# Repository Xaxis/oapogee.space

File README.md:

# oApogee

An open source telemetry payload for model rockets, and the documentation that
teaches you to build one. Site at **[oapogee.space](https://oapogee.space)**.

oApogee records altitude, acceleration and orientation through a flight, logs it
to onboard flash, and optionally downlinks it live over LoRa and reports GNSS
position for recovery. It attaches to a rocket you already own, in a printed pod
that needs no modification to the airframe.

**oApogee is a passive instrumentation payload. It does not fire ejection
charges, control deployment, ignite motors, or command any pyrotechnic device.**
That is a design boundary and it will not change. See
[content/safety.md](content/safety.md).

## Project status

**Nothing physical exists.** No board has been fabricated, assembled, weighed,
priced, or flown, so every cost, mass, range and endurance figure is missing
rather than estimated. Each gap is marked in place, on the page that would
otherwise state the figure, rather than summarised on a page of its own: a count
drifts, a marker beside the number it replaces does not.

What does exist is further along than a paper design. The circuit is source that
routes; the firmware is sixteen host-testable modules with a test suite in CI;
the two wire formats are published specifications with a second implementation
checked against the first byte for byte; the printed parts are parametric
source. No fabrication package is published, because the check that gates it
refuses while the board has an open blocker, and it does.

Design decisions that are still open are in
[docs/open-questions.md](docs/open-questions.md).

## The rule everything else follows from

**Never publish a number that has not been measured or sourced.**

The documentation is the product. The hardware is commodity: barometer, IMU,
microcontroller, radio, all of it available to anyone. What makes this project
worth existing is that a motivated beginner can follow the site start to finish
and end up with a working payload and a real flight graph. That only works if
every number on it is true.

So there are no estimates dressed as measurements, and that is enforced rather
than promised: `make prose` fails on any physical quantity in published prose
that is not either recorded in an allowlist with where it came from, or sitting
inside a marker that says what evidence would close it. A site full of confident
fabricated specs is worse than useless in a hobby where people's build decisions
depend on them.

Two consequences you will notice immediately: the bill of materials has no
prices in it, and the homepage does not have a flight graph.

## Layout

```
content/     Prose pages, Markdown with YAML frontmatter
data/        Structured source: bom, tiers, glossary, preflight, troubleshooting,
             system diagram, flight phases, mechanical, suppliers, flights
docs/        The page map, open questions, and the two wire format specs
hardware/    tscircuit circuit source and OpenSCAD printed parts. Runs under bun.
firmware/    Freestanding C11 core and its host test suite. Needs only cmake.
apps/web/    Next.js 15 App Router site, one renderer of content/ and data/
tools/       The checks, and the generators that feed them
```

`content/` and `data/` are the product. `apps/web/` renders them. Anything that
appears in more than one place on the site lives in `data/` as YAML, never as a
hand-written table inside a Markdown page, because two hand-written tables drift
and nothing catches it.

## Commands

Everything is a `make` target, and CI runs the same ones. `make` lists them.

```bash
make install     # dependencies, pinned to match CI
make dev         # the site, locally
make check       # everything CI runs
make check-fast  # the same without the site build
make hw          # re-render the board artifacts from hardware/oapogee.tsx
make fw-test     # build and run the firmware test suite
```

## Contributing

The most useful contribution to this project right now is telling us where it is
wrong. The safety and regulatory pages in particular are written carefully and
have not been reviewed by anyone with formal expertise in the rules they
describe.

Read [CONTRIBUTING.md](CONTRIBUTING.md) first, then
[CONTENT-STYLE.md](CONTENT-STYLE.md). Between them they cover the accuracy rule,
the voice, and the naming conventions, all of which are enforced in CI.

## Naming

The project is **oApogee**: lowercase `o`, capital `A`, one word. The `o` stands
for open.

**It is never shortened to "Apogee."** Apogee Components is the dominant
retailer in model rocketry and owns that word in this hobby completely. There is
no short form. oApogee is not affiliated with Apogee Components.

The three tiers are oApogee Solo, oApogee Link, and oApogee Track.

## Licence

Three, because this repository holds three different kinds of thing.

| What | Licence | SPDX |
|---|---|---|
| Hardware design files | CERN Open Hardware Licence v2, Strongly Reciprocal | `CERN-OHL-S-2.0` |
| Firmware and software | Apache License 2.0 | `Apache-2.0` |
| Documentation and content | Creative Commons Attribution-ShareAlike 4.0 | `CC-BY-SA-4.0` |

Full texts in [LICENSES/](LICENSES), and [LICENSE](LICENSE) says which applies
to which files and why. Reciprocal on the board because the plausible bad
outcome is a closed volume clone; permissive on the firmware because that is the
part worth having other people embed everywhere.

**The design is open. The name is not.** Build it, sell it, fork it, call it
something else. Licences do not stop somebody shipping a clone under this name;
a trademark does.

A project named for openness that ships a black box loses the audience it was
built for, so the bar is source files rather than exports: the KiCad project
rather than a PDF schematic, the parametric CAD source rather than only STLs,
and the full firmware including its calibration constants. All three are
published. Anything that cannot be opened will be declared explicitly rather
than quietly omitted.

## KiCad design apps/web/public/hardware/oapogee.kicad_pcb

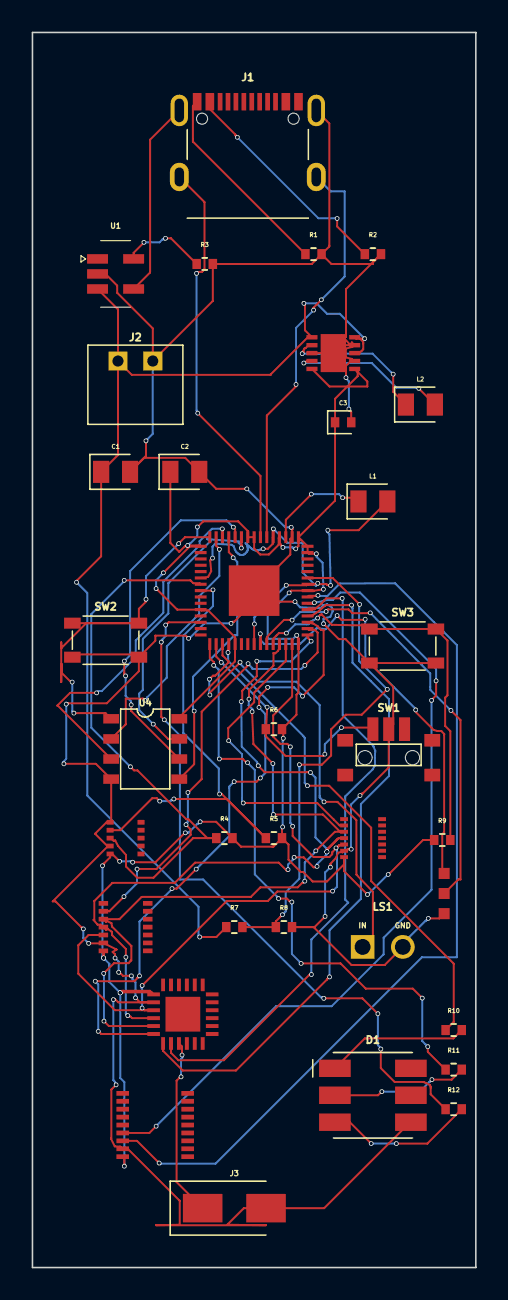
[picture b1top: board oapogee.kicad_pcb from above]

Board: 2 copper layers, 28.0 x 78.0 mm, 35 parts (0 on the bottom side), 44 nets.

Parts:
C1, C2: 10uF; capacitor_cap0805
C3: 100nF; capacitor_cap0402
D1: RGB-LED-CC
J1: USB-C-16P
J2: S2B-PH-K-S
J3: ANT-902-928
J4: SWD-PADS
L1: 3.3µH; inductor_0805
L2: 2.2µH; inductor_0805
LS1: PIEZO-BUZZER
R1, R2: 5.1kΩ; resistor_res0402
R3, R9: 10kΩ; resistor_res0402
R4, R5: 4.7kΩ; resistor_res0402
R6, R7, R8: 100kΩ; resistor_res0402
R10: 330Ω; resistor_res0402
R11, R12: 220Ω; resistor_res0402
SW1: ARM-SWITCH
SW2: BOOT-BUTTON
SW3: RESET-BUTTON
U1: MCP73831
U2: TPS63001
U3: RP2350A
U4: W25Q128JVSIQ
U5: BMP390
U6: ICM-42688-P
U7: ADXL375
U8: SX1262
U9: MAX-M10S

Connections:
.J1 .CC1 to .R1 .pin1: J1.5, R1.1
.J1 .CC2 to .R2 .pin1: J1.6, R2.1
.J1 .DM to .U3 .USB_DM: J1.4, U3.51
.J1 .DP to .U3 .USB_DP: J1.3, U3.52
.J1 .VBUS to .U1 .VDD: J1.1, U1.4
.J4 .SWCLK to .U3 .SWCLK: J4.1, U3.24
.J4 .SWDIO to .U3 .SWDIO: J4.2, U3.25
.R7 .pin2 to .U3 .VBAT_SENSE: R7.2, R8.1, U3.40
.R10 .pin2 to .D1 .A_R: D1.1, R10.2
.R11 .pin2 to .D1 .A_G: D1.2, R11.2
.R12 .pin2 to .D1 .A_B: D1.3, R12.2
.SW1 .A to .U3 .ARM: R6.1, SW1.1, U3.17
.SW2 .A1 to .U3 .QSPI_CS: SW2.1, SW2.2, U3.60, U4.1
.SW3 .A1 to .U3 .RUN: R9.2, SW3.1, SW3.2, U3.26
.U1 .PROG to .R3 .pin1: R3.1, U1.5
.U2 .L1 to .L2 .pin1: L2.1, U2.4
.U2 .L2 to .L2 .pin2: L2.2, U2.2
.U3 .BUZZER to .LS1 .IN: LS1.1, U3.18
.U3 .CS_HIGHG to .U7 .CS: U3.32, U7.6
.U3 .CS_IMU to .U6 .CS: U3.28, U6.6
.U3 .CS_RADIO to .U8 .NSS: U3.33, U8.6
.U3 .GNSS_RX to .U9 .TXD: U3.37, U9.3
.U3 .GNSS_TX to .U9 .RXD: U3.36, U9.4
.U3 .LED_B to .R12 .pin1: R12.1, U3.13
.U3 .LED_G to .R11 .pin1: R11.1, U3.16
.U3 .LED_R to .R10 .pin1: R10.1, U3.19
.U3 .QSPI_D0 to .U4 .DI: U3.57, U4.5
.U3 .QSPI_D1 to .U4 .DO: U3.59, U4.2
.U3 .QSPI_D2 to .U4 .WP: U3.58, U4.3
.U3 .QSPI_D3 to .U4 .HOLD: U3.55, U4.7
.U3 .QSPI_SCK to .U4 .CLK: U3.56, U4.6
.U3 .RADIO_BUSY to .U8 .BUSY: U3.34, U8.7
.U3 .RADIO_DIO1 to .U8 .DIO1: U3.35, U8.8
.U3 .SCL to .U5 .SCL: R5.1, U3.8, U5.4
.U3 .SDA to .U5 .SDA: R4.1, U3.7, U5.3
.U3 .SPI_MISO to .U6 .SDO: U3.27, U6.5, U7.5, U8.5
.U3 .SPI_MOSI to .U6 .SDI: U3.31, U6.4, U7.4, U8.4
.U3 .SPI_SCK to .U6 .SCLK: U3.29, U6.3, U7.3, U8.3
.U3 .VREG_LX to .L1 .pin1: L1.1, U3.48
.U8 .ANT to .J3 .ANT: J3.1, U8.9
GND: C1.2, C2.2, C3.2, D1.4, J1.2, J2.2, J3.2, J4.3, LS1.2, R1.2, R2.2, R3.2, R8.2, SW1.2, SW2.3, SW2.4, SW3.3, SW3.4, U1.2, U2.3, U2.7, U2.9, U2.11, U3.47, U3.61, U4.4, U5.2, U5.5, U6.2, U7.2, U8.2, U9.2
V3V3: C2.1, C3.1, R4.2, R5.2, R6.2, R9.1, U2.1, U2.10, U3.1, U3.11, U3.20, U3.30, U3.38, U3.44, U3.45, U3.46, U3.49, U3.53, U3.54, U4.8, U5.1, U6.1, U7.1, U8.1, U9.1
VBAT: C1.1, J2.1, R7.1, U1.3, U2.5, U2.6, U2.8
VCORE: L1.2, U3.6, U3.23, U3.39, U3.50
